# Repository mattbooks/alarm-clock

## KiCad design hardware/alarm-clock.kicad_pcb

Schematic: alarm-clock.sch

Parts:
BT1: 3V; CR2032_SMD
C1: 10µF; C_1206_HandSoldering
C2: 1µF; C_1206_HandSoldering
C3, C4: 20pF; C_1206_HandSoldering
CON1, CON2: BARREL_JACK
D1: D; D_1206
D2: LED; LED_1206
J1: CONN_01X04; Pin_Header_Straight_1x04_Pitch2.54mm
P1: PROGRAMMER; Pin_Header_Straight_2x03_Pitch2.54mm
PB1, PB2, PB3: push_button; KS_BUTTON
Q1, Q2: Q_NPN_BCE; SOT-23_Handsoldering
R1, R2: 3k3; R_1206_HandSoldering
R3, R4, R5: 2k2; R_1206_HandSoldering
SP1: BUZZER; Buzzer_12x9.5RM7.6
SW1: SPST; SW_Micro_SPST
U1: LM7805CT; TO-220_Horizontal
U2: DS3232; SOIC-20W_7.5x12.8mm_Pitch1.27mm
U3: ATMEGA328-AU; TQFP-32_7x7mm_Pitch0.8mm
Y1: 16MHz; Crystal_HC49-U_Vertical

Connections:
+5V: C2.1, D1.2 (A), J1.1, P1.2, Q2.2 (C), R3.1, R4.1, R5.1, U1.3 (OUT), U2.4, U3.4, U3.18
GND: BT1.2, C1.2, C2.2, C3.1, C4.1, CON1.2, CON1.3, J1.2, P1.6, PB1.2, PB2.2, PB3.2, Q1.2 (C), SP1.2, SW1.2, U1.2 (GND), U2.1, U2.2, U2.7, U2.8, U2.9, U2.10, U2.11, U2.12, U2.13, U2.14, U2.15, U3.3, U3.5
unnamed: BT1.1, U2.16
unnamed: C3.2, U3.7, Y1.2
unnamed: C4.2, U3.8, Y1.1
unnamed: CON2.2, CON2.3, Q1.3 (E)
unnamed: D2.1 (K), SW1.3
unnamed: D2.2 (A), R3.2
unnamed: Q1.1 (B), R1.2
unnamed: Q2.1 (B), R2.2
unnamed: Q2.3 (E), SP1.1
PB1: R1.1, U3.13
PB3: P1.4, R2.1, U3.15
PB4: P1.1, U3.16
PB5: P1.3, U3.17
PD0: PB1.1, U3.30
PD1: PB2.1, U3.31
PD2: PB3.1, U3.32
PD3: SW1.1, U3.1
RESET: P1.5, U3.29
SCL: J1.4, R4.2, U2.18, U3.28
SDA: J1.3, R5.2, U2.17, U3.27
VPP: C1.1, CON1.1, CON2.1, D1.1 (K), U1.1 (IN)

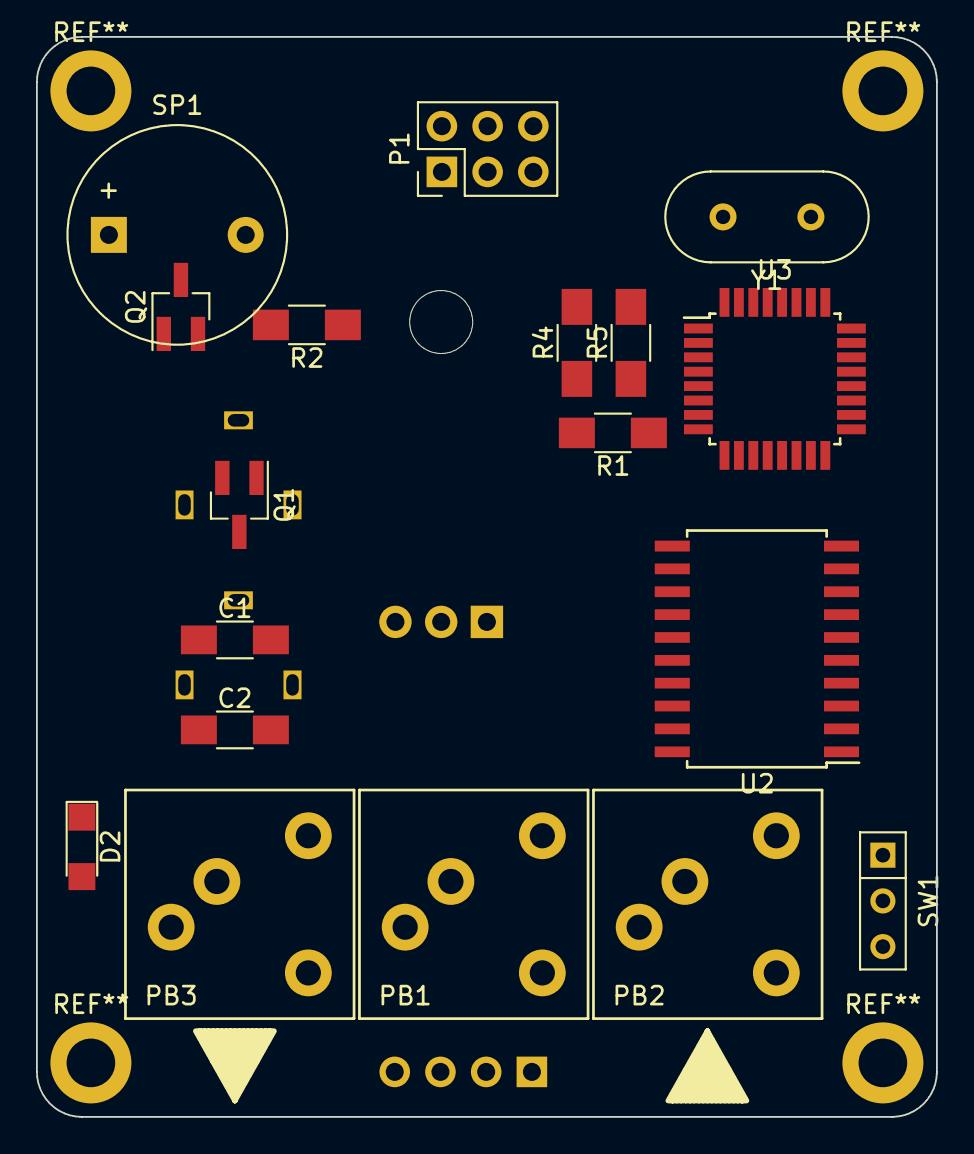
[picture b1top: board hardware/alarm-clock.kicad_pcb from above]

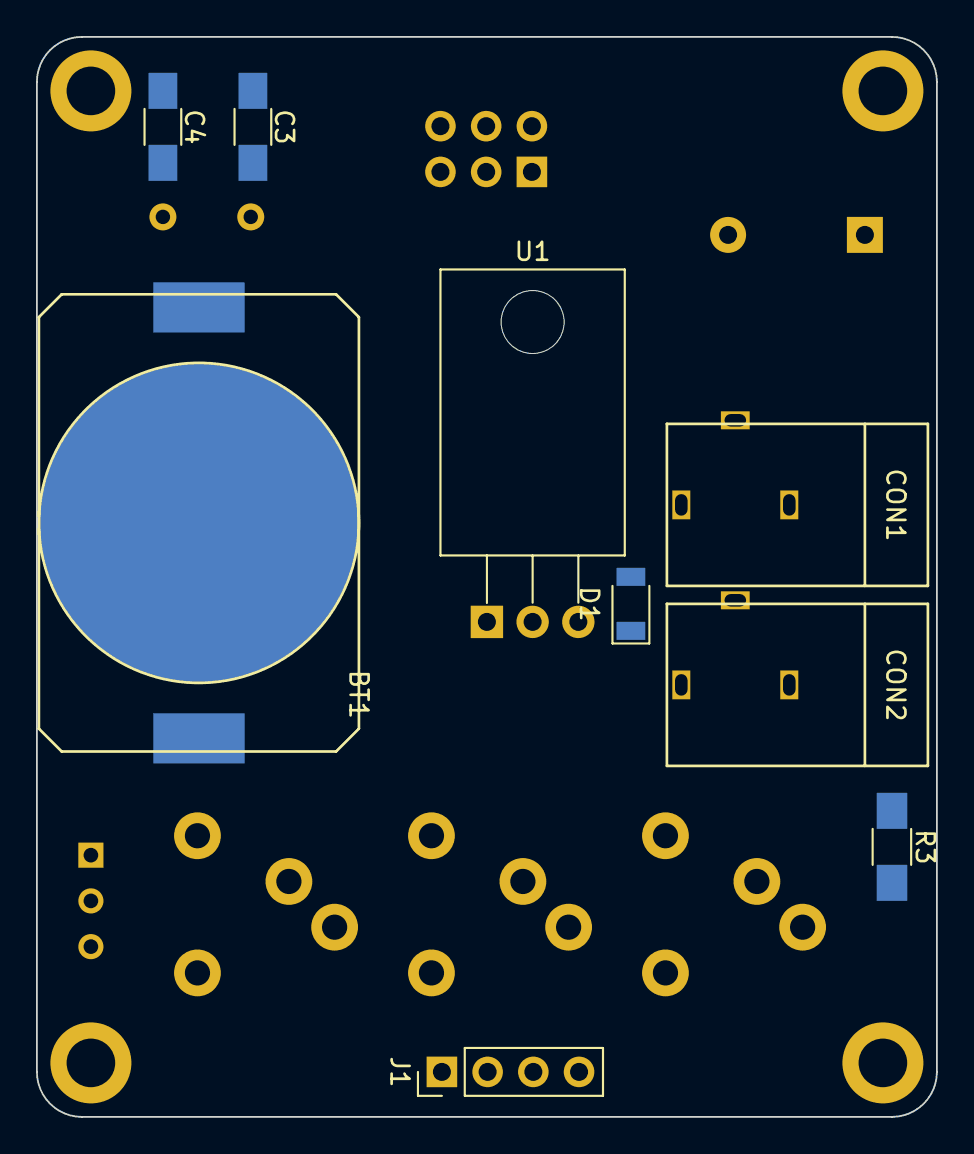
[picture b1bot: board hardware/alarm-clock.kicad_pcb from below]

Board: 2 copper layers, 50.0 x 60.0 mm, 27 parts (9 on the bottom side), 23 nets, no tracks yet.

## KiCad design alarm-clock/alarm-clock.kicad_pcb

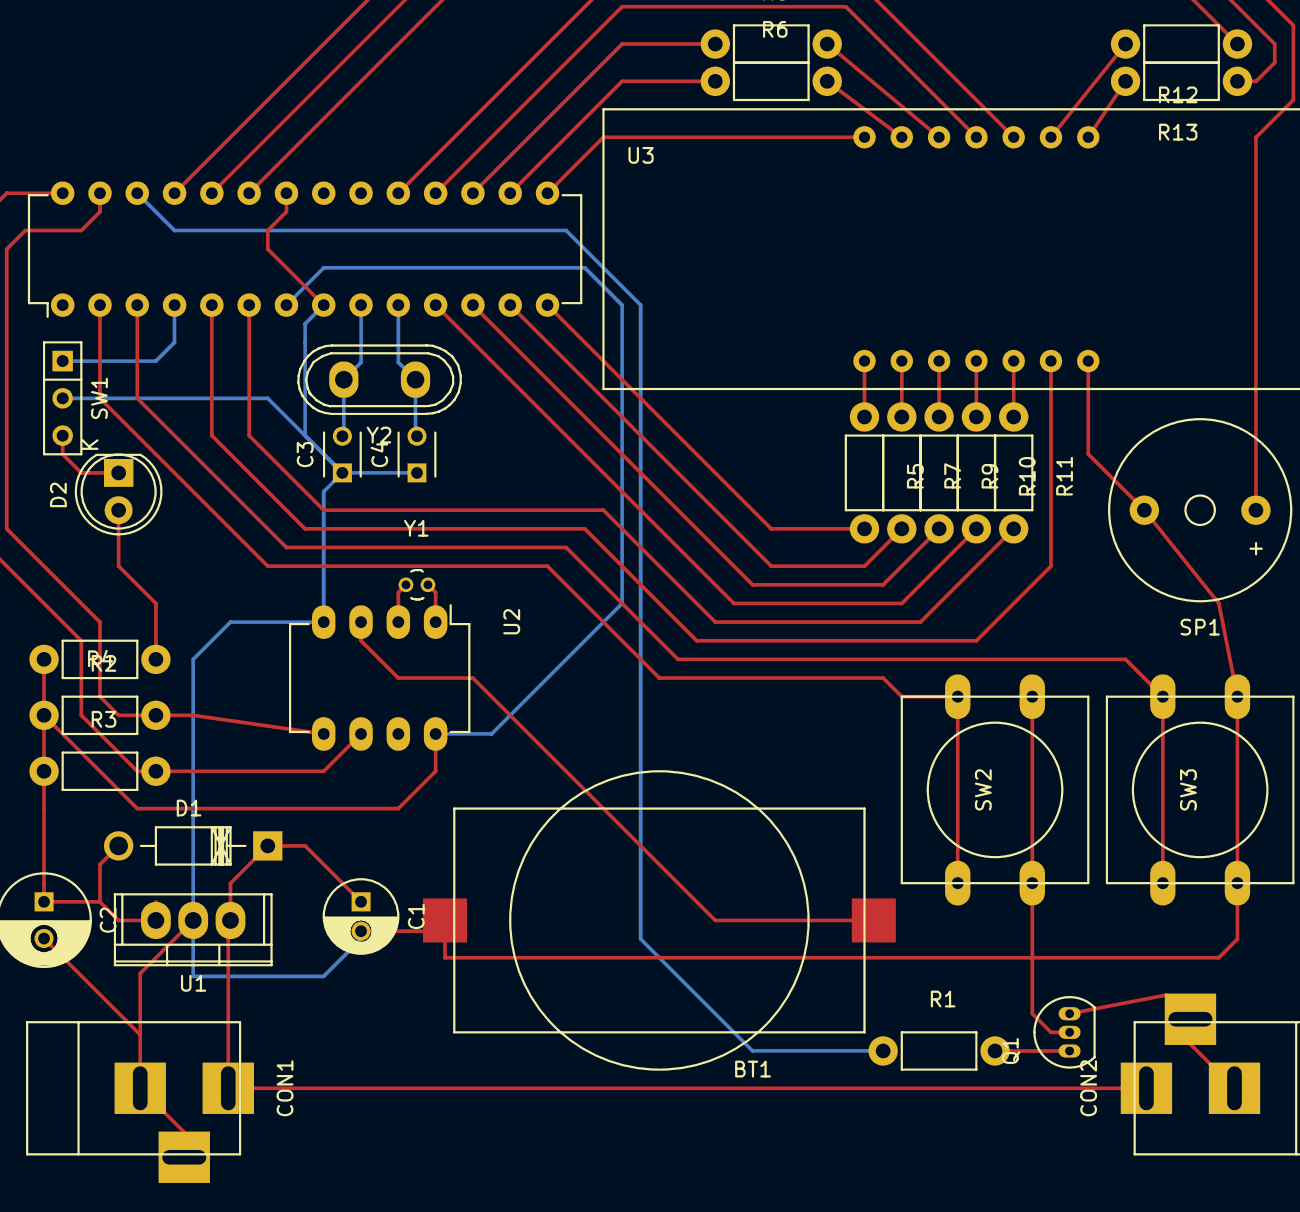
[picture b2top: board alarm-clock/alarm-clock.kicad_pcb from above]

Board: 2 copper layers, 33 parts (0 on the bottom side), 41 nets.

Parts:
BT1: 3V; CR2032
C1: 10µF; C_Radial_D5_L11_P2
C2: 1µF; C_Radial_D6.3_L11.2_P2.5
C3, C4: 20pF; C_Disc_D3_P2.5
CON1, CON2: BARREL_JACK
D1: D; Diode_DO-41_SOD81_Horizontal_RM10
D2: LED; LED-5MM
IC1: ATMEGA328-P; DIP-28_W7.62mm
Q1: Q_NPN_BCE; TO-92_Inline_Narrow_Oval
R1: 3.3k; Resistor_Horizontal_RM7mm
R2, R3, R5, R6, R7, R8, R9, R10, R11, R12, R13: 2.2k; Resistor_Horizontal_RM7mm
R4: 270; Resistor_Horizontal_RM7mm
SP1: BUZZER; Buzzer_12x9.5RM7.6
SW1: SWITCH_INV; SW_Micro_SPST
SW2, SW3: SW_PUSH; SW_PUSH-12mm
U1: LM7805CT; TO-220
U2: DS1307; DIP-8_W7.62mm_LongPads
U3: 4Dig7Seg
Y1: 38.7kHz; Crystal_Round_Vertical_2mm
Y2: 16MHz; Crystal_HC50-U_Vertical

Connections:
+5V: C2.1, D1.2, IC1.7, R2.1, R3.1, R4.1, U1.3, U2.8
GND: BT1.2, C1.2, C2.2, C3.1, C4.1, CON1.2, CON1.3, IC1.8, IC1.22, Q1.2, SP1.2, SW1.2, SW2.2, SW3.2, U1.2, U2.4, U3.7
unnamed: BT1.1, U2.3
unnamed: C3.2, IC1.9, Y2.2
unnamed: C4.2, IC1.10, Y2.1
unnamed: CON2.2, CON2.3, Q1.3
unnamed: D2.1, SW1.3
unnamed: D2.2, R4.2
unnamed: Q1.1, R1.2
unnamed: R5.1, U3.1
unnamed: R6.2, U3.13
unnamed: R7.1, U3.2
unnamed: R8.2, U3.12
unnamed: R9.1, U3.3
unnamed: R10.1, U3.4
unnamed: R11.1, U3.5
unnamed: R12.2, U3.9
unnamed: R13.2, U3.8
unnamed: U2.1, Y1.2
unnamed: U2.2, Y1.1
PB0: IC1.14, R5.2
PB1: IC1.15, U3.14
PB2: IC1.16, R6.1
PB3: IC1.17, R8.1
PB4: IC1.18, U3.11
PB5: IC1.19, U3.10
PC0: IC1.23, R12.1
PC1: IC1.24, R13.1
PC2: IC1.25, SP1.1
PC3: IC1.26, R1.1
PC4: IC1.27, R2.2, U2.5
PC5: IC1.28, R3.2, U2.6
PD0: IC1.2, SW2.1
PD1: IC1.3, SW3.1
PD2: IC1.4, SW1.1
PD3: IC1.5, U3.6
PD4: IC1.6, R11.2
PD5: IC1.11, R10.2
PD6: IC1.12, R9.2
PD7: IC1.13, R7.2
VPP: C1.1, CON1.1, CON2.1, D1.1, U1.1

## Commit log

2016-10-18 Blinky lights
2016-10-23 Remove dependency on pololu
2016-10-23 Re-organize
2016-10-23 Schematic first pass
2016-10-29 Import RTC library + support
2016-10-29 Update interrupt names
2016-11-07 Schematic refactoring/progress
2016-11-09 Add Adafruit Eagle libs
2016-11-09 Add 4Dig7Seg + CR2032 components
2016-11-09 Update and V1 of PCB
2016-11-09 Add Gerber output
2016-11-09 Rename folders
2016-11-10 Update schematic
2016-12-18 reorg
2016-12-19 Move PCB labels
2016-12-20 Retarget m328p
2017-01-02 Updated schematic w/ SMD and working buzzer
2017-01-16 add hardware libs
2017-01-16 Cleanup source and fix compile warns
2017-01-16 ignore cache lib
2017-01-16 ignore rescue.lib
2017-01-16 Update PCB silkscreen
2017-01-16 Cleanup and update some footprints
2017-01-17 Reorgannize source and fix Makefile betterer
2017-01-19 remove executable flags
2017-01-19 Swap uart library
2017-01-19 Add timekeeping
2017-01-19 Button structure
2017-01-19 Redo loop for adding button polling
2017-01-20 WIP Adding control flow
2017-01-21 WIP Cleaning up schematic
2017-01-31 move time functions
2017-01-31 time change demo that almost works
2017-02-04 Swap rtc tm for c lib tm
2017-02-04 Add unit tests for time functions
2017-02-04 Add BARREL_JACK with smaller pads
2017-02-04 Updated gerbers
2017-02-04 Add programmer port
2017-02-04 Add GND fills
2017-02-04 Update gerbs
2017-02-23 ignore ctags
2017-02-23 Retarget m328 because derp
2017-02-23 Implement more of the control state machine
2017-02-23 Only read time if we care what it is
2017-03-05 Add PC3 as output
2017-03-15 Re-wire to use hardware PWM d'oh
2017-03-15 WIP Add alarm and light control
2017-04-15 WIP on V3
2017-04-16 WIP V3
2017-06-11 Add alarm functionality
2017-06-11 Turn on lights before alarm
2018-08-04 Try to fix time jumping during setting
2018-08-04 Faster key repeat
2018-08-04 Remove unused function
2018-08-04 Set hour and minute separately for clock
2018-08-05 Fix time corrupting when setting alarm
